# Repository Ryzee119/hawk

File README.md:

## Hawk - Open Source Xbox Live Communicator

This project is an open source replacement of the [Microsoft Xbox Live Communicator](https://xbox.fandom.com/wiki/Xbox_LIVE_Headset) utilizing modern components and custom open-source firmware.

It provides feature parity with the original communicator with the following differences:
* A 3.5mm TRRS jack is used to support more generic headsets. (Stereo headsets will output as mono.)
* The volume wheel is replaced with a button. Volume is indicated by LED brightness.

### Usage
* When installing Hawk into your controller, it must be installed in the slot closest to you.
* Press the button to increment the volume. Once maximum volume is reached, it will cycle back to zero.
* Hold the button for 1 second to mute and disable the microphone input (LED will flash at 1Hz).
* Hold the button 2 seconds to enter microphone gain adjustment mode (LED will flash at 4Hz).
* Volume and microphone gain adjustments will be saved internally. You can reset these to default by holding the button down for 8 seconds.

### Assembly
* **When ordering PCB thickness should be 1.2mm!**
* See [Kitspace](https://master.staging.kitspace.dev/Ryzee119/hawk) for BOM, PCB ordering and assembly information.
* See [KiCanvas](https://kicanvas.org/?github=https%3A%2F%2Fgithub.com%2FRyzee119%2Fhawk%2Ftree%2Fmaster%2Fhardware) for schematic view.
* See [Tracespace](https://tracespace.io/view/?boardUrl=https://raw.githubusercontent.com/Ryzee119/hawk/refs/heads/master/.kitspace/hawk-gerber.zip) for Gerber view.

### Compilation
* Download and install [Visual Studio Code](https://code.visualstudio.com/).
* Install the [PlatformIO IDE](https://platformio.org/platformio-ide) plugin.
* In Visual Studio Code File > Open Folder... > hawk
* Hit build on the Platform IO toolbar (✓).

### Programming
* [Compile](https://github.com/Ryzee119/hawk?tab=readme-ov-file#compilation) or [Download](https://github.com/Ryzee119/hawk/releases) the pre-built firmware image.
* USB DFU. Connect an xbox controller to your PC, then hold the Hawk button down while inserting it into the controller to enter DFU mode. Your PC should detect this. you can then program with [STM32Cubeprogrammer](https://www.st.com/en/development-tools/stm32cubeprog.html)
* ST-Link interface (5 pin header available on PCB)

### FAQ
* What is the pinout of the headphone jack?
  * Hawk's headphone jack is wired as per [CTIA standard TRRS](https://upload.wikimedia.org/wikipedia/commons/e/ee/3.5mm_TRRS_phone_connector_with_CTIA_standard.png). There is another less common standard called OMTP. This will not work but adapters are available.
* It doesn't fit in my controller slot.
  * PCB should be manufactured with 1.2mm thickness. Most fabrication houses default to 1.6mm so be careful!
* Microphone is really quiet.
  * You can increase the microphone gain above default. Hold the Hawk button down for more than 2 seconds to enter gain adjustment mode. The LED will blink 4 times per second to show it is in the right mode then press the button to increase the gain. Hold for 1 second to exit. If this is still too quiet, you can modify the `MAX_MICROPHONE_GAIN` variable and recompile the code to bump it up even higher.
* Speaker is really quiet
  * Adjust the volume by pressing the button until the LED is at its maximum brightness. Unfortunately, it is already compiled to the maximum allowable by Hawk. If it is still too quiet, your headset's impedance may be too low.
* Does this work on modern controller adapters (ogx360, wingman etc)?
  * Not really, but kind of. To do this, you must connect a USB 1.1 compliant hub to the Xbox player port. Your controller then connects to port 1 of this hub and Hawk to port 2.
* LED just flashes constantly when connected
  * This means the main IC cannot communicate with the audio codec on Hawk. This is likely a soldering issue.
* `Error: Database: There's no active configuration for this device.` when programming.
  * Try an earlier revision of STM32CubeProgrammer. Users have reported some success with `v2.5.0`.

### Attribution
* [Board outline](https://github.com/Zeigren/OXC)
* [EEPROM emulation code](https://github.com/nimaltd/ee)

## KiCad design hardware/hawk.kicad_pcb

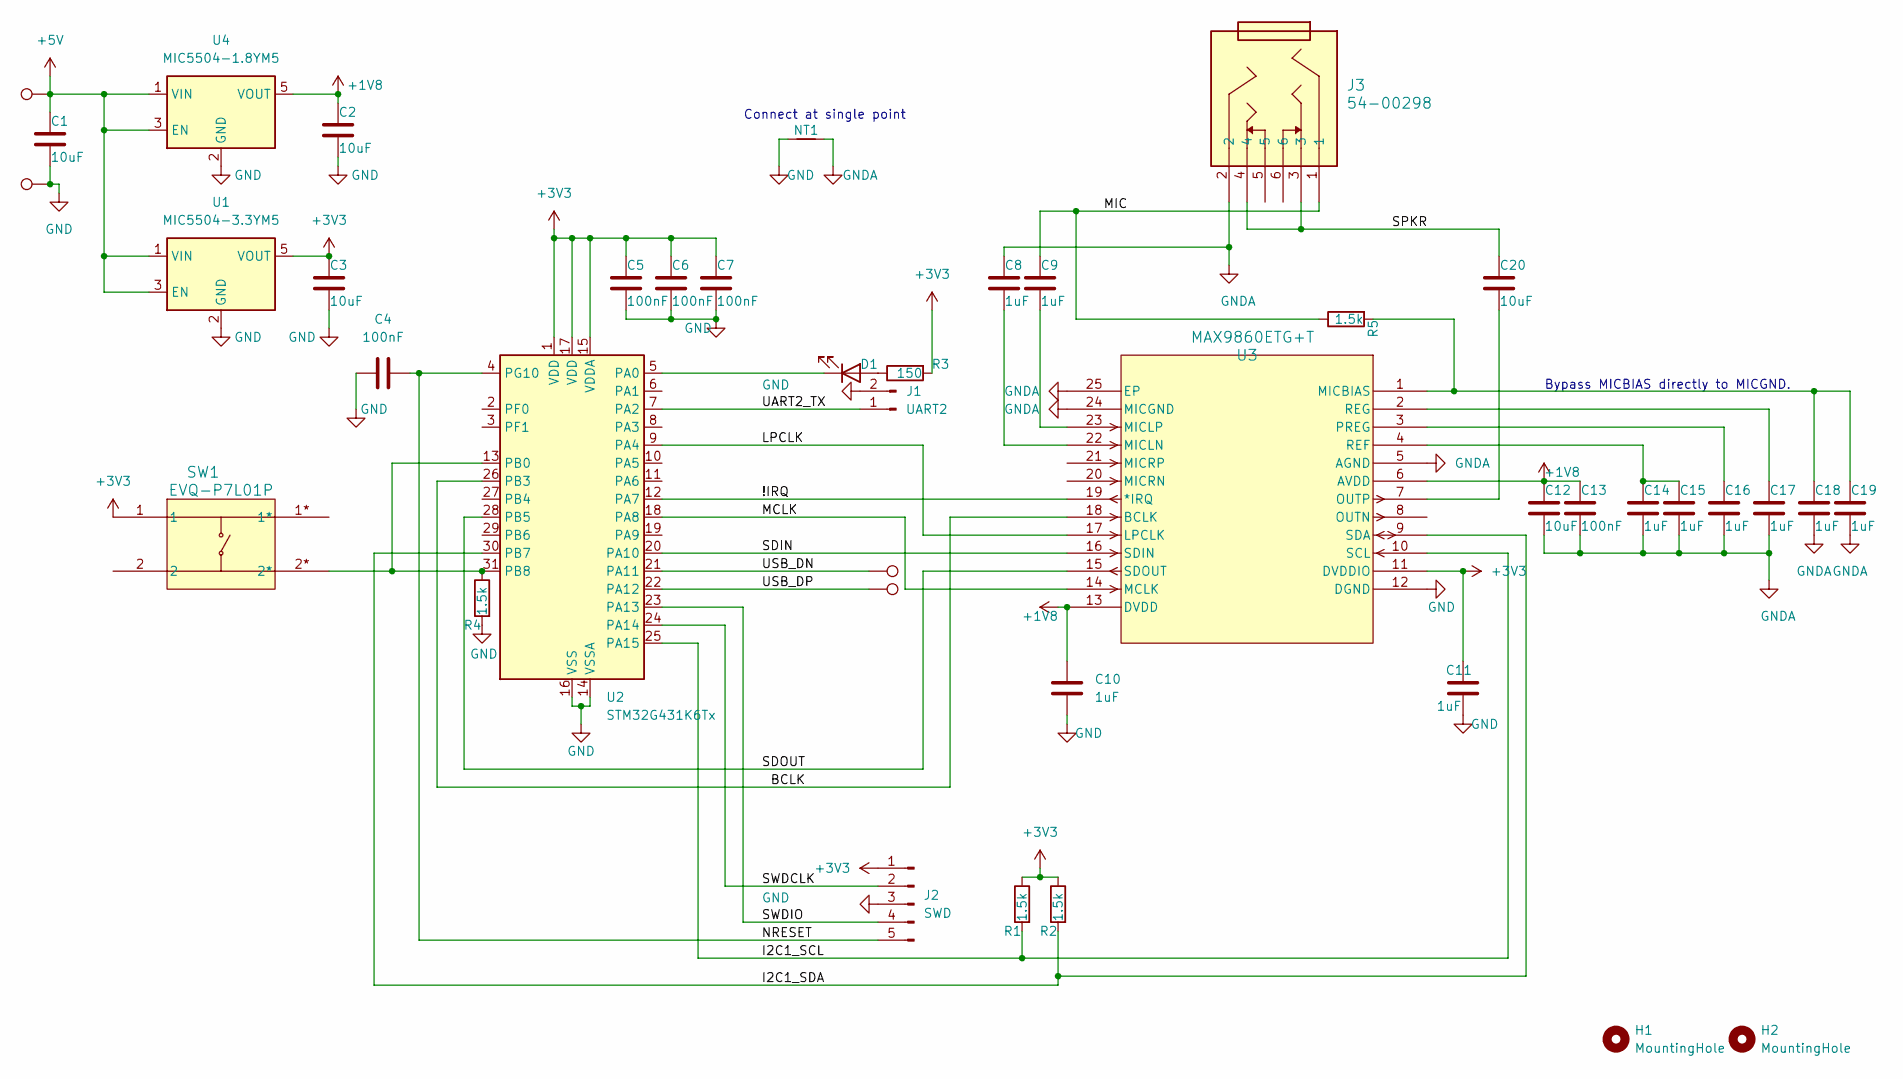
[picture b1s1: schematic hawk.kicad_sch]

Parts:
C1, C2, C3, C12, C20: 10uF; C_0603_1608Metric_Pad1.08x0.95mm_HandSolder
C4, C5, C6, C7, C13: 100nF; C_0603_1608Metric_Pad1.08x0.95mm_HandSolder
C8, C9, C10, C11, C14, C15, C16, C17, C18, C19: 1uF; C_0603_1608Metric_Pad1.08x0.95mm_HandSolder
D1: LED; LED_0603_1608Metric_Pad1.05x0.95mm_HandSolder
H1, H2: MountingHole; MountingHole_3.2mm_M3
J1: UART2; PinHeader_1x02_P2.54mm_Vertical
J2: SWD; PinHeader_1x05_P2.54mm_Vertical
J3: 54-00298
NT1: NetTie_2; NetTie-2_THT_Pad1.0mm
R1, R2, R4, R5: 1.5k; R_0603_1608Metric_Pad0.98x0.95mm_HandSolder
R3: 150; R_0603_1608Metric_Pad0.98x0.95mm_HandSolder
SW1: EVQ-P7L01P; EVQ_P7_PAN
TP1: USB_5V; TestPoint_Pad_1.0x1.0mm
TP2: USB_GND; TestPoint_Pad_1.0x1.0mm
TP3: USB_DM; TestPoint_Pad_1.0x1.0mm
TP4: USB_DP; TestPoint_Pad_1.0x1.0mm
U1: MIC5504-3.3YM5; SOT-23-5
U2: STM32G431K6Tx; LQFP-32_7x7mm_P0.8mm
U3: MAX9860ETG+T; 21-0139I_T2444-4_MXM
U4: MIC5504-1.8YM5; SOT-23-5

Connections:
+1V8: C2.1, C10.1, C12.1, C13.1, U3.6 (AVDD), U3.13 (DVDD), U4.5 (VOUT)
+3V3: C3.1, C5.1, C6.1, C7.1, C11.1, J2.1, R1.1, R2.1, R3.2, SW1.1, U1.5 (VOUT), U2.1 (VDD), U2.15 (VDDA), U2.17 (VDD), U3.11 (DVDDIO)
+5V: C1.1, TP1.1, U1.1 (VIN), U1.3 (EN), U4.1 (VIN), U4.3 (EN)
/!IRQ: U2.12 (PA7), U3.19 (*IRQ)
/BCLK: U2.26 (PB3), U3.18 (BCLK)
/I2C1_SCL: R1.2, U2.25 (PA15), U3.10 (SCL)
/I2C1_SDA: R2.2, U2.30 (PB7), U3.9 (SDA)
/LPCLK: U2.9 (PA4), U3.17 (LPCLK)
/MCLK: U2.18 (PA8), U3.14 (MCLK)
/MIC: C9.1, J3.1, R5.1
/NRESET: C4.1, J2.5, U2.4 (PG10)
/SDIN: U2.20 (PA10), U3.16 (SDIN)
/SDOUT: U2.28 (PB5), U3.15 (SDOUT)
/SPKR: C20.1, J3.3, J3.4
/SWDCLK: J2.2, U2.24 (PA14)
/SWDIO: J2.4, U2.23 (PA13)
/UART2_TX: J1.1, U2.7 (PA2)
/USB_DN: TP3.1, U2.21 (PA11)
/USB_DP: TP4.1, U2.22 (PA12)
GND: C1.2, C2.2, C3.2, C4.2, C5.2, C6.2, C7.2, C10.2, C11.2, J1.2, J2.3, NT1.1, R4.2, TP2.1, U1.2 (GND), U2.14 (VSSA), U2.16 (VSS), U2.32 (VSS), U3.12 (DGND), U4.2 (GND)
GNDA: C8.1, C12.2, C13.2, C14.2, C15.2, C16.2, C17.2, C18.2, C19.2, J3.2, NT1.2, U3.5 (AGND), U3.24 (MICGND), U3.25 (EP)
unnamed: D1.2 (A), R3.1
unnamed: D1.1 (K), U2.5 (PA0)
unnamed: R4.1, SW1.2*, U2.13 (PB0), U2.31 (PB8)
unnamed: C18.1, C19.1, R5.2, U3.1 (MICBIAS)
unnamed: C8.2, U3.22 (MICLN)
unnamed: C9.2, U3.23 (MICLP)
unnamed: C20.2, U3.7 (OUTP)
unnamed: C16.1, U3.3 (PREG)
unnamed: C14.1, C15.1, U3.4 (REF)
unnamed: C17.1, U3.2 (REG)

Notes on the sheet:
Connect at single point
Bypass MICBIAS directly to MICGND.

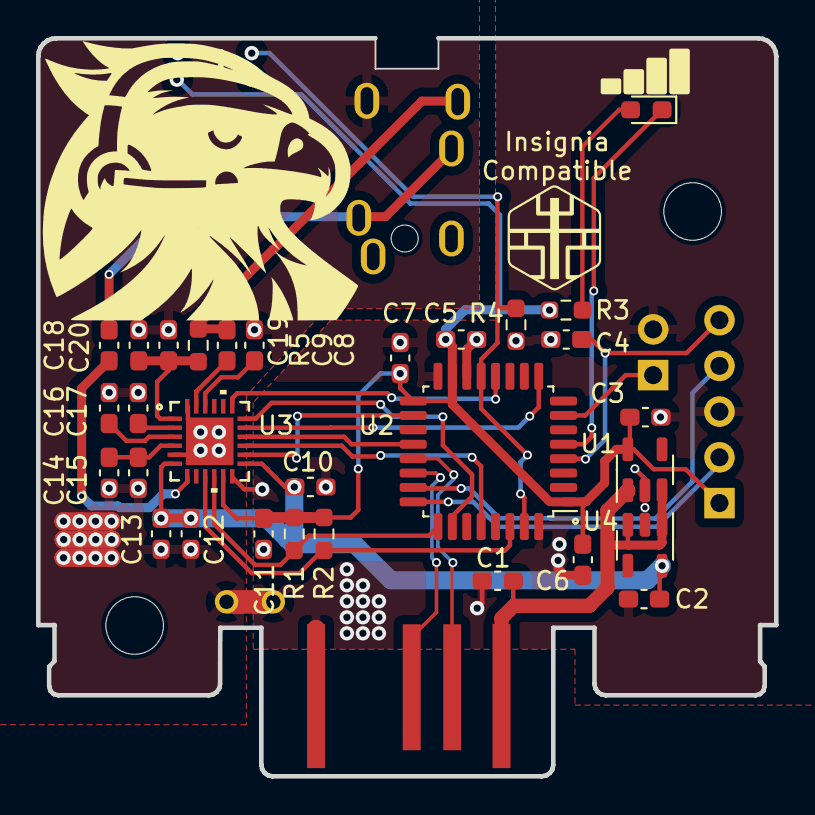
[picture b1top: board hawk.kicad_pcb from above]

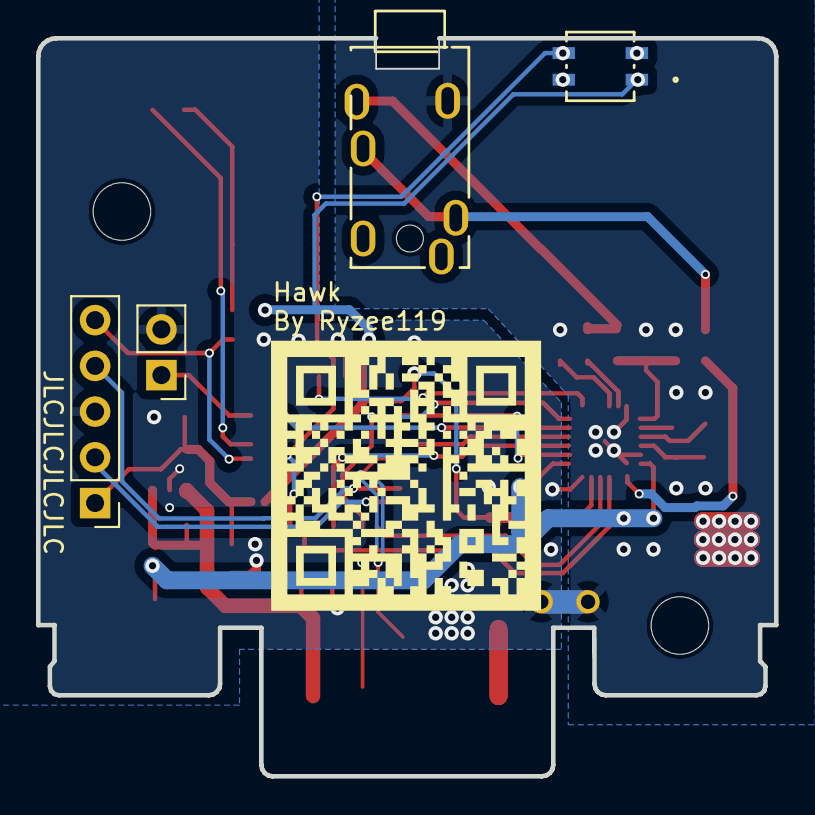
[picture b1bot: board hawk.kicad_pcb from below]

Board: 2 copper layers, 41.0 x 41.0 mm, 41 parts (4 on the bottom side), 31 nets.

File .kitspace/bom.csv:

Reference,Qty,Description,Part Number,Manufacturer,Digikey,LCSC
U1,1,IC REG LINEAR 3.3V 300MA SOT23-5,MIC5504-3.3YM5,Microchip Technology,576-4764-1-ND,C3021093
U2,1,IC MCU 32BIT 32KB FLASH 32LQFP,STM32G431K6T6,STMicroelectronics,497-STM32G431K6T6-ND,C730097
U3,1,IC CODEC MONO AUD 16BIT 24TQFN,MAX9860ETG+T,Maxim Integrated,MAX9860ETG+TCT-ND,C516787
U4,1,IC REG LINEAR 1.8V 300MA SOT23-5,MIC5504-1.8YM5,Microchip Technology,576-4879-1-ND,C626116
"C1, C2, C3, C12, C20",5,CAP CER 10uF 0603,CAP CER 10uF 0603,ANY,311-1448-1-ND,C19702
"C4, C5, C6, C7, C13",5,CAP CER 100nF 0603,CAP CER 100nF 0603,ANY,311-1088-1-ND,C30926
"C8, C9, C10, C11, C14, C15, C16, C17, C18, C19",10,CAP CER 1uF 0603,CAP CER 1uF 0603,ANY,311-1446-1-ND,C15849
"R1, R2, R4, R5",4,RES SMD 1.5K OHM 1% 1/10W 0603,RES SMD 1.5K OHM 1% 1/10W 0603,ANY,118-CR0603-FX-1501ELFCT-ND,C114668
R3,1,RES SMD 150 OHM 1% 1/10W 0603,RES SMD 150 OHM 1% 1/10W 0603,ANY,118-CR0603-FX-1500ELFCT-ND,C114608
D1,1,LED 2V 20MA 0603,LED 2V 20MA 0603,ANY,3147-B1911PG--20D000514U1930CT-ND,C5123548
J3,1,CONN JACK TRRS 3.5MM,54-00298,Tensility International Corp,839-54-00298CT-ND,C707261
SW1,1,SWITCH TACTILE SPST-NO MOM,EVQ-P7L01P,Panasonic Electronic Components,P16769CT-ND,C79168

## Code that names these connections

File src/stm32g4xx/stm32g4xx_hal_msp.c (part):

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    __HAL_RCC_GPIOA_CLK_ENABLE();
    __HAL_RCC_GPIOB_CLK_ENABLE();
    /**I2C1 GPIO Configuration
    PA15     ------> I2C1_SCL
    PB7     ------> I2C1_SDA
    */
    GPIO_InitStruct.Pin = GPIO_PIN_15;
    GPIO_InitStruct.Mode = GPIO_MODE_AF_OD;
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    __HAL_RCC_I2C1_CLK_DISABLE();

    /**I2C1 GPIO Configuration
    PA15     ------> I2C1_SCL
    PB7     ------> I2C1_SDA
    */
    HAL_GPIO_DeInit(GPIOA, GPIO_PIN_15);

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
    __HAL_RCC_GPIOA_CLK_ENABLE();
    /**TIM2 GPIO Configuration
    PA0     ------> TIM2_CH1
    */
    GPIO_InitStruct.Pin = LED_Pin;
    GPIO_InitStruct.Mode = GPIO_MODE_AF_PP;
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
    __HAL_RCC_GPIOA_CLK_ENABLE();
    /**USART2 GPIO Configuration
    PA2     ------> USART2_TX
    PA3     ------> USART2_RX
    */
    GPIO_InitStruct.Pin = GPIO_PIN_2|GPIO_PIN_3;
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    __HAL_RCC_USART2_CLK_DISABLE();

    /**USART2 GPIO Configuration
    PA2     ------> USART2_TX
    PA3     ------> USART2_RX
    */
    HAL_GPIO_DeInit(GPIOA, GPIO_PIN_2|GPIO_PIN_3);
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    SAI1_client ++;

    /**SAI1_A_Block_A GPIO Configuration
    PA10     ------> SAI1_SD_A
    */
    GPIO_InitStruct.Pin = SD_TX_Pin;
    GPIO_InitStruct.Mode = GPIO_MODE_AF_PP;
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    SAI1_client ++;

    /**SAI1_B_Block_B GPIO Configuration
    PA4     ------> SAI1_FS_B
    PB3     ------> SAI1_SCK_B
    PB5     ------> SAI1_SD_B
    */
    GPIO_InitStruct.Pin = FS_LRCLK_Pin;
    GPIO_InitStruct.Mode = GPIO_MODE_AF_PP;
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      }

    /**SAI1_A_Block_A GPIO Configuration
    PA10     ------> SAI1_SD_A
    */
    HAL_GPIO_DeInit(SD_TX_GPIO_Port, SD_TX_Pin);

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      }

    /**SAI1_B_Block_B GPIO Configuration
    PA4     ------> SAI1_FS_B
    PB3     ------> SAI1_SCK_B
    PB5     ------> SAI1_SD_B
    */
    HAL_GPIO_DeInit(FS_LRCLK_GPIO_Port, FS_LRCLK_Pin);

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
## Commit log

2024-03-29 Hardware: Initial Commit
2024-04-27 Hardware: Reduce locking tab
2024-04-27 kitspace: Remove duplicate entry
2024-04-27 Add installation slot note
2024-04-27 Remove double xbox
2024-04-27 kitspace: Seems it expects gerbers extracted, also missing summary in yaml
2024-04-27 Update kit space link
2024-04-27 Add note about PCB thickness
2024-04-28 Firmware: Flash on codec init fail
2024-04-28 README: Add FAQ
2024-04-28 README: Fix formatting of bullets
2024-04-28 README: Add note about blinking LED on boot failure
2024-04-29 README: Add link to release section
2024-05-04 README: more clarity on programming
2024-05-11 hardware: Tweak to TRRS footprint
2024-08-02 README: Update FAQ
2025-03-16 bom: Update switch to low N, without boss
2025-03-16 README: Include direct link to Gerber View

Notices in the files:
src/stm32g4xx/stm32g4xx_hal_msp.c:
Copyright (c) 2024 STMicroelectronics.
All rights reserved.
This software is licensed under terms that can be found in the LICENSE file
